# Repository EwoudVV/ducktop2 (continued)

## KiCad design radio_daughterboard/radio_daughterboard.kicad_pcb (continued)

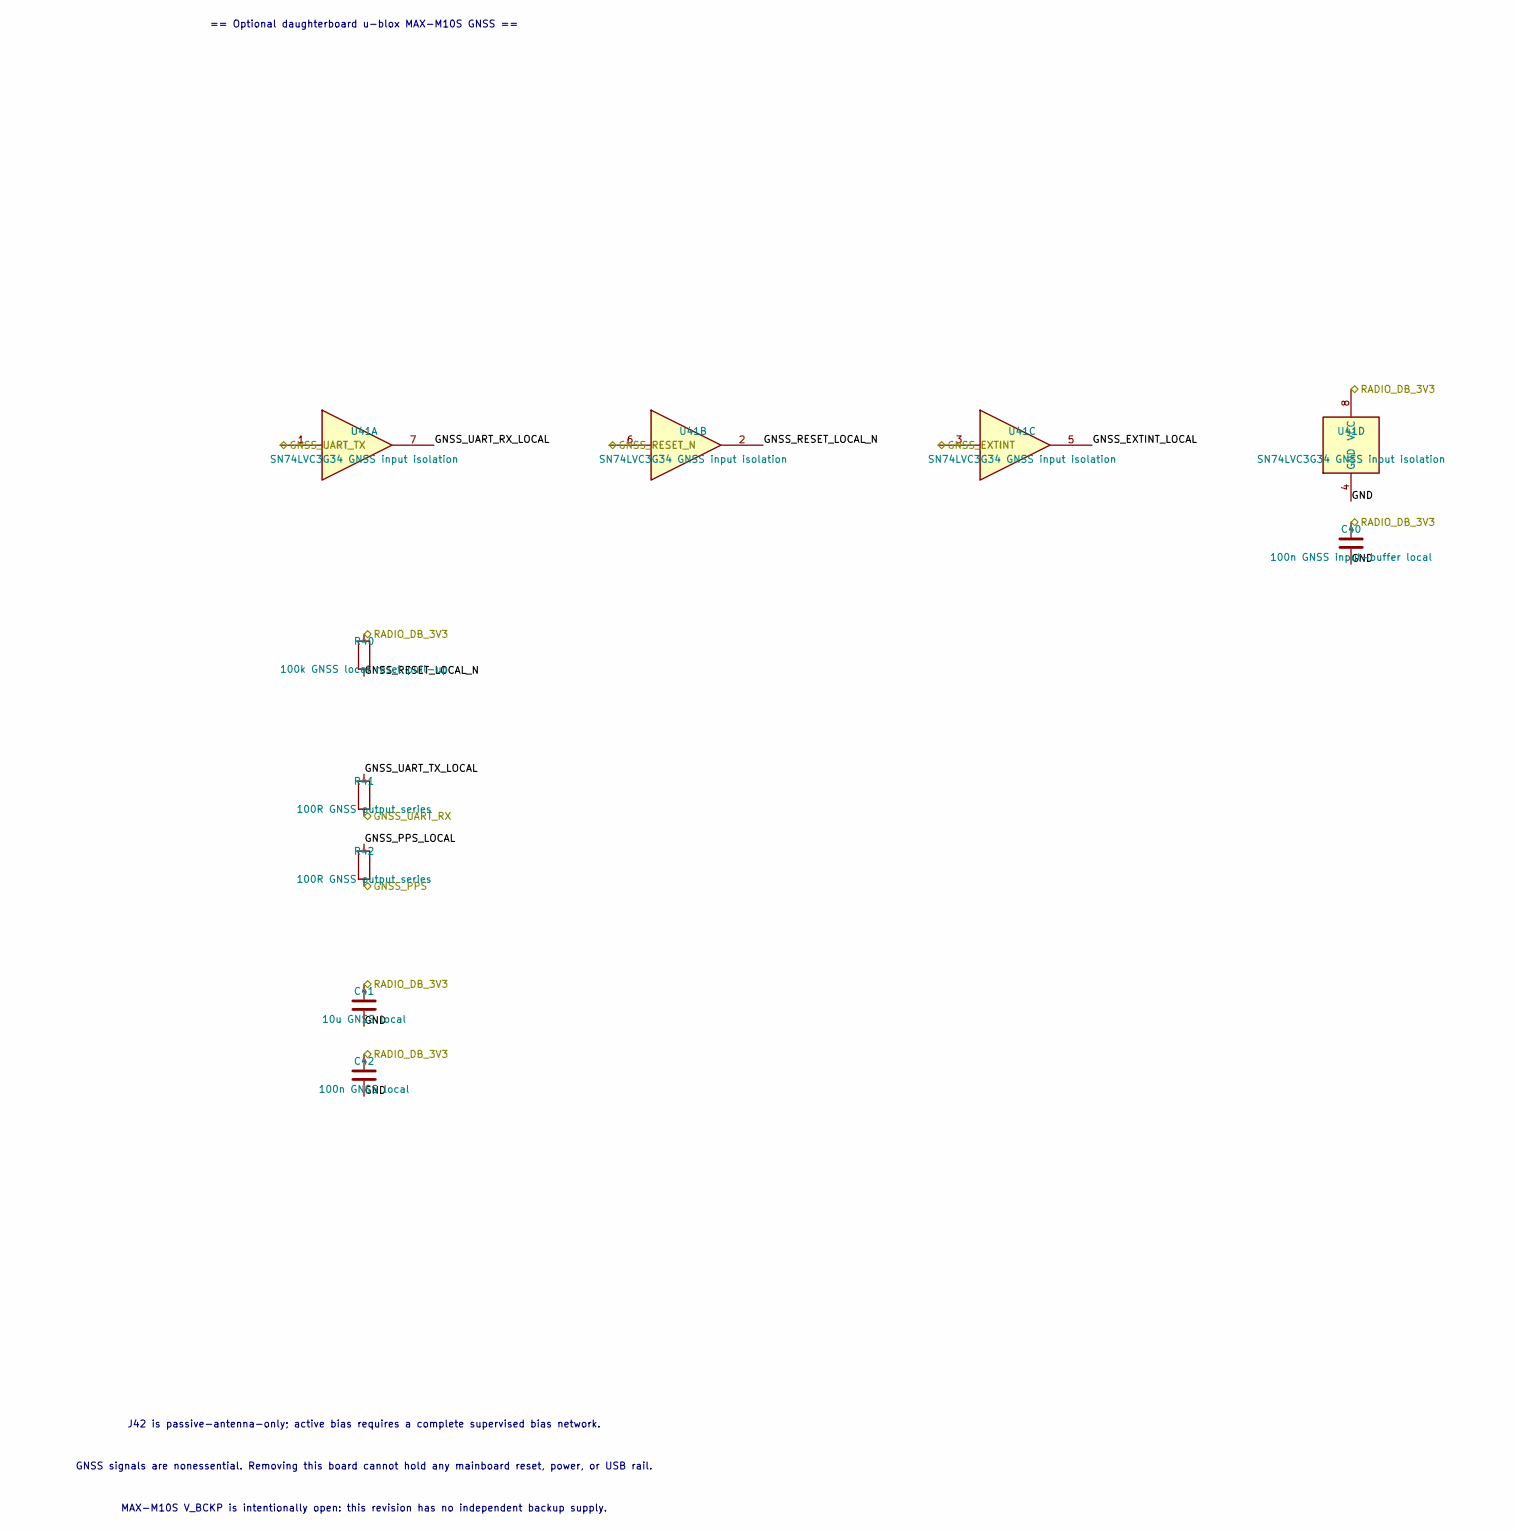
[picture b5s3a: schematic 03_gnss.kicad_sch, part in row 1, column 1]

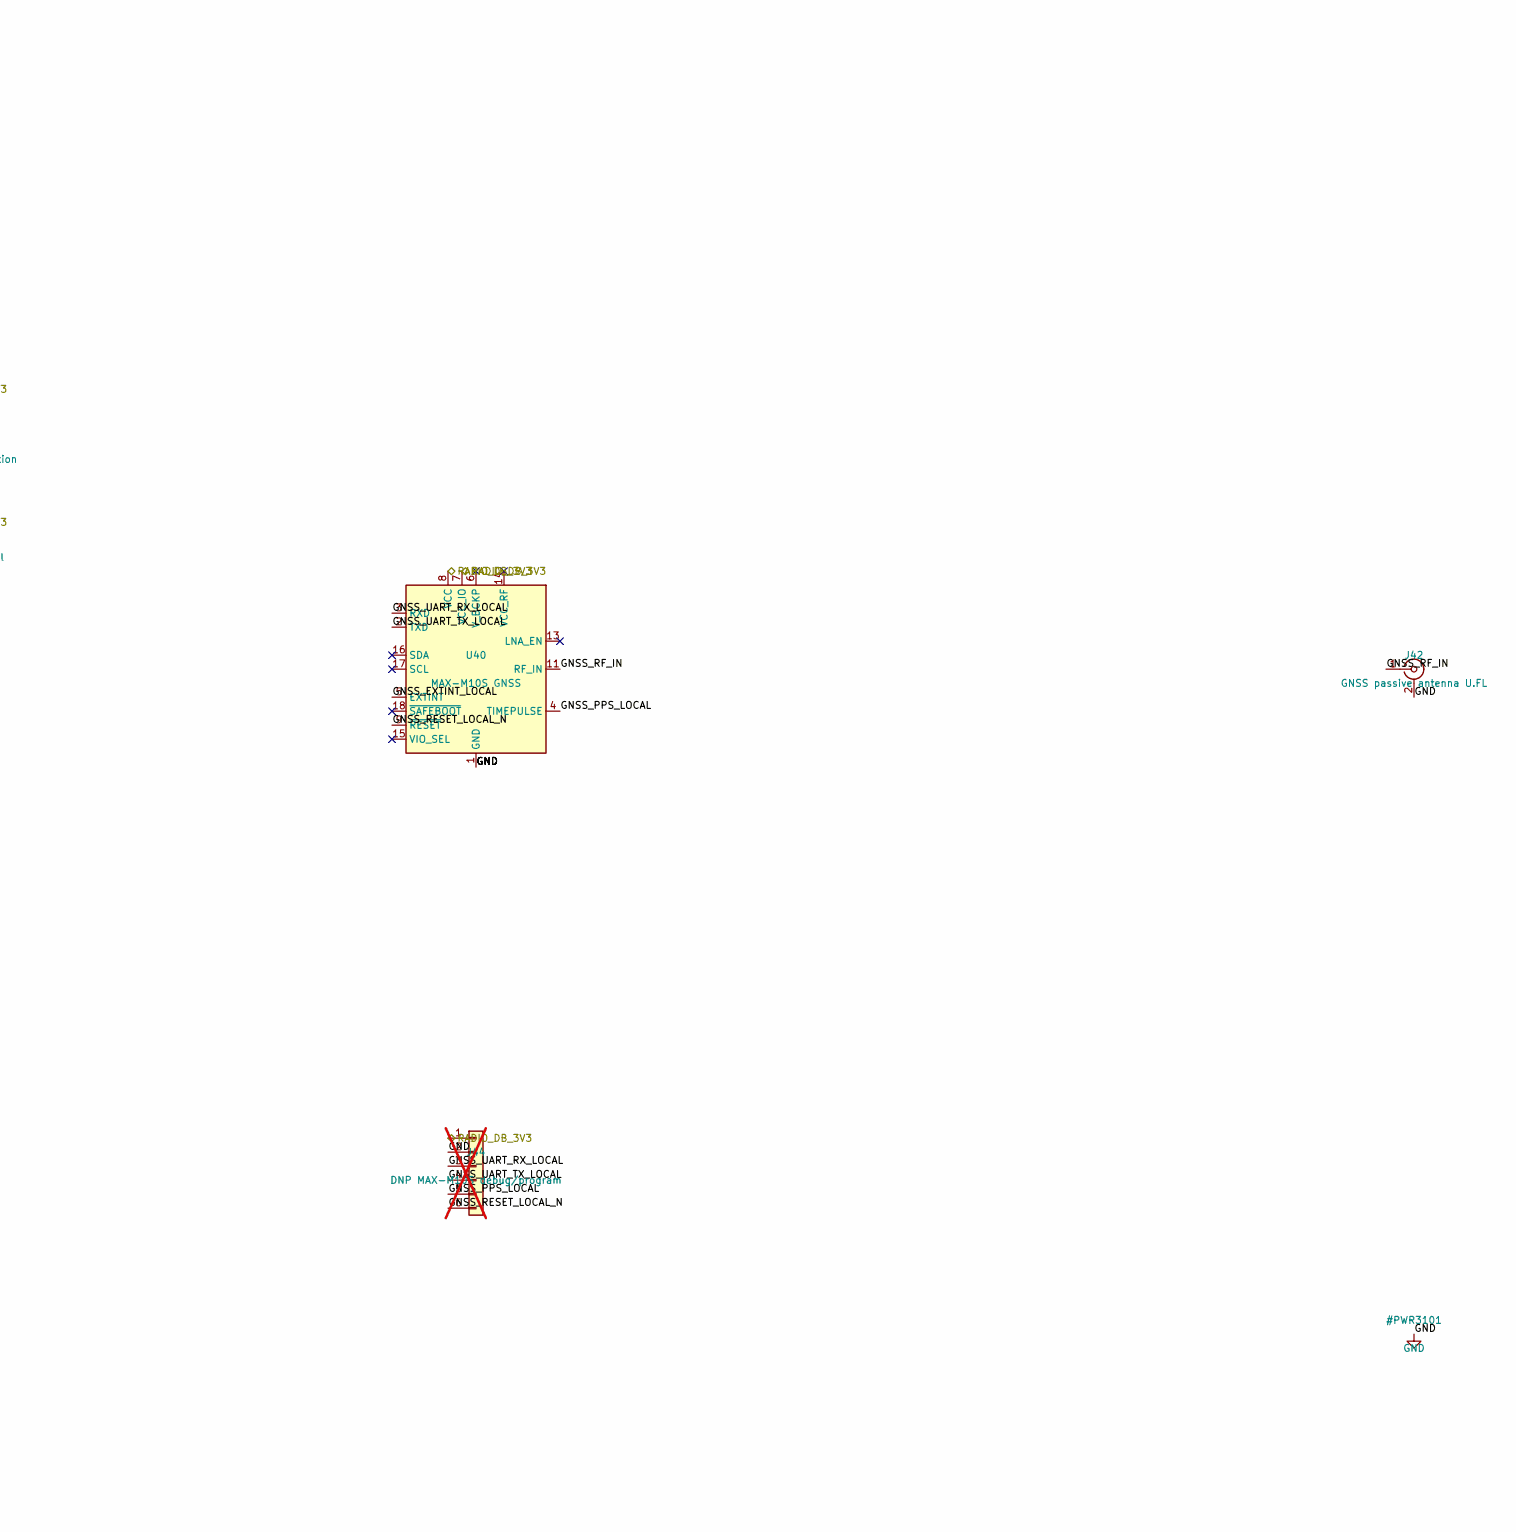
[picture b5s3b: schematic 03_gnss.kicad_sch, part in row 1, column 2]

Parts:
C40: 100n GNSS input-buffer local; C_0603_1608Metric; MPN GRM188R71H104KA93D
C41: 10u GNSS local; C_1206_3216Metric; MPN GRM31CR71E106KA12L
C42: 100n GNSS local; C_0603_1608Metric; MPN GRM188R71H104KA93D
J42: GNSS passive antenna U.FL; U.FL_Hirose_U.FL-R-SMT-1_Vertical; MPN U.FL-R-SMT-1(01)
J44: DNP MAX-M10S debug/program; PinHeader_1x06_P2.54mm_Vertical; not fitted
R40: 100k GNSS local reset pull-up; R_0603_1608Metric; MPN RC0603FR-07100KL
R41, R42: 100R GNSS output series; R_0603_1608Metric; MPN RC0603FR-07100RL
U40: MAX-M10S GNSS; ublox_MAX; MPN MAX-M10S-00B
U41: SN74LVC3G34 GNSS input isolation; VSSOP-8_2.3x2mm_P0.5mm; MPN SN74LVC3G34DCUR

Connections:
/GNSS/GNSS_EXTINT_LOCAL: U40.5 (EXTINT), U41.5
/GNSS/GNSS_PPS_LOCAL: J44.5, R42.1, U40.4 (TIMEPULSE)
/GNSS/GNSS_RESET_LOCAL_N: J44.6, R40.2, U40.9 (~RESET), U41.2
/GNSS/GNSS_RF_IN: J42.1 (In), U40.11 (RF_IN)
/GNSS/GNSS_UART_RX_LOCAL: J44.3, U40.3 (RXD), U41.7
/GNSS/GNSS_UART_TX_LOCAL: J44.4, R41.1, U40.2 (TXD)
/GNSS_EXTINT: U41.3; also elsewhere on the board
/GNSS_PPS: R42.2; also elsewhere on the board
/GNSS_RESET_N: U41.6; also elsewhere on the board
/GNSS_UART_RX: R41.2; also elsewhere on the board
/GNSS_UART_TX: U41.1; also elsewhere on the board
/RADIO_DB_3V3: C40.1, C41.1, C42.1, J44.1, R40.1, U40.7 (VCC_IO), U40.8 (VCC), U41.8 (VCC); also elsewhere on the board
GND: C40.2, C41.2, C42.2, J42.2 (Ext), J44.2, U40.1 (GND), U40.10 (GND), U40.12 (GND), U41.4 (GND); also elsewhere on the board

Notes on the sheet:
== Optional daughterboard u-blox MAX-M10S GNSS ==
J42 is passive-antenna-only; active bias requires a complete supervised bias network.
GNSS signals are nonessential. Removing this board cannot hold any mainboard reset, power, or USB rail.
MAX-M10S V_BCKP is intentionally open: this revision has no independent backup supply.

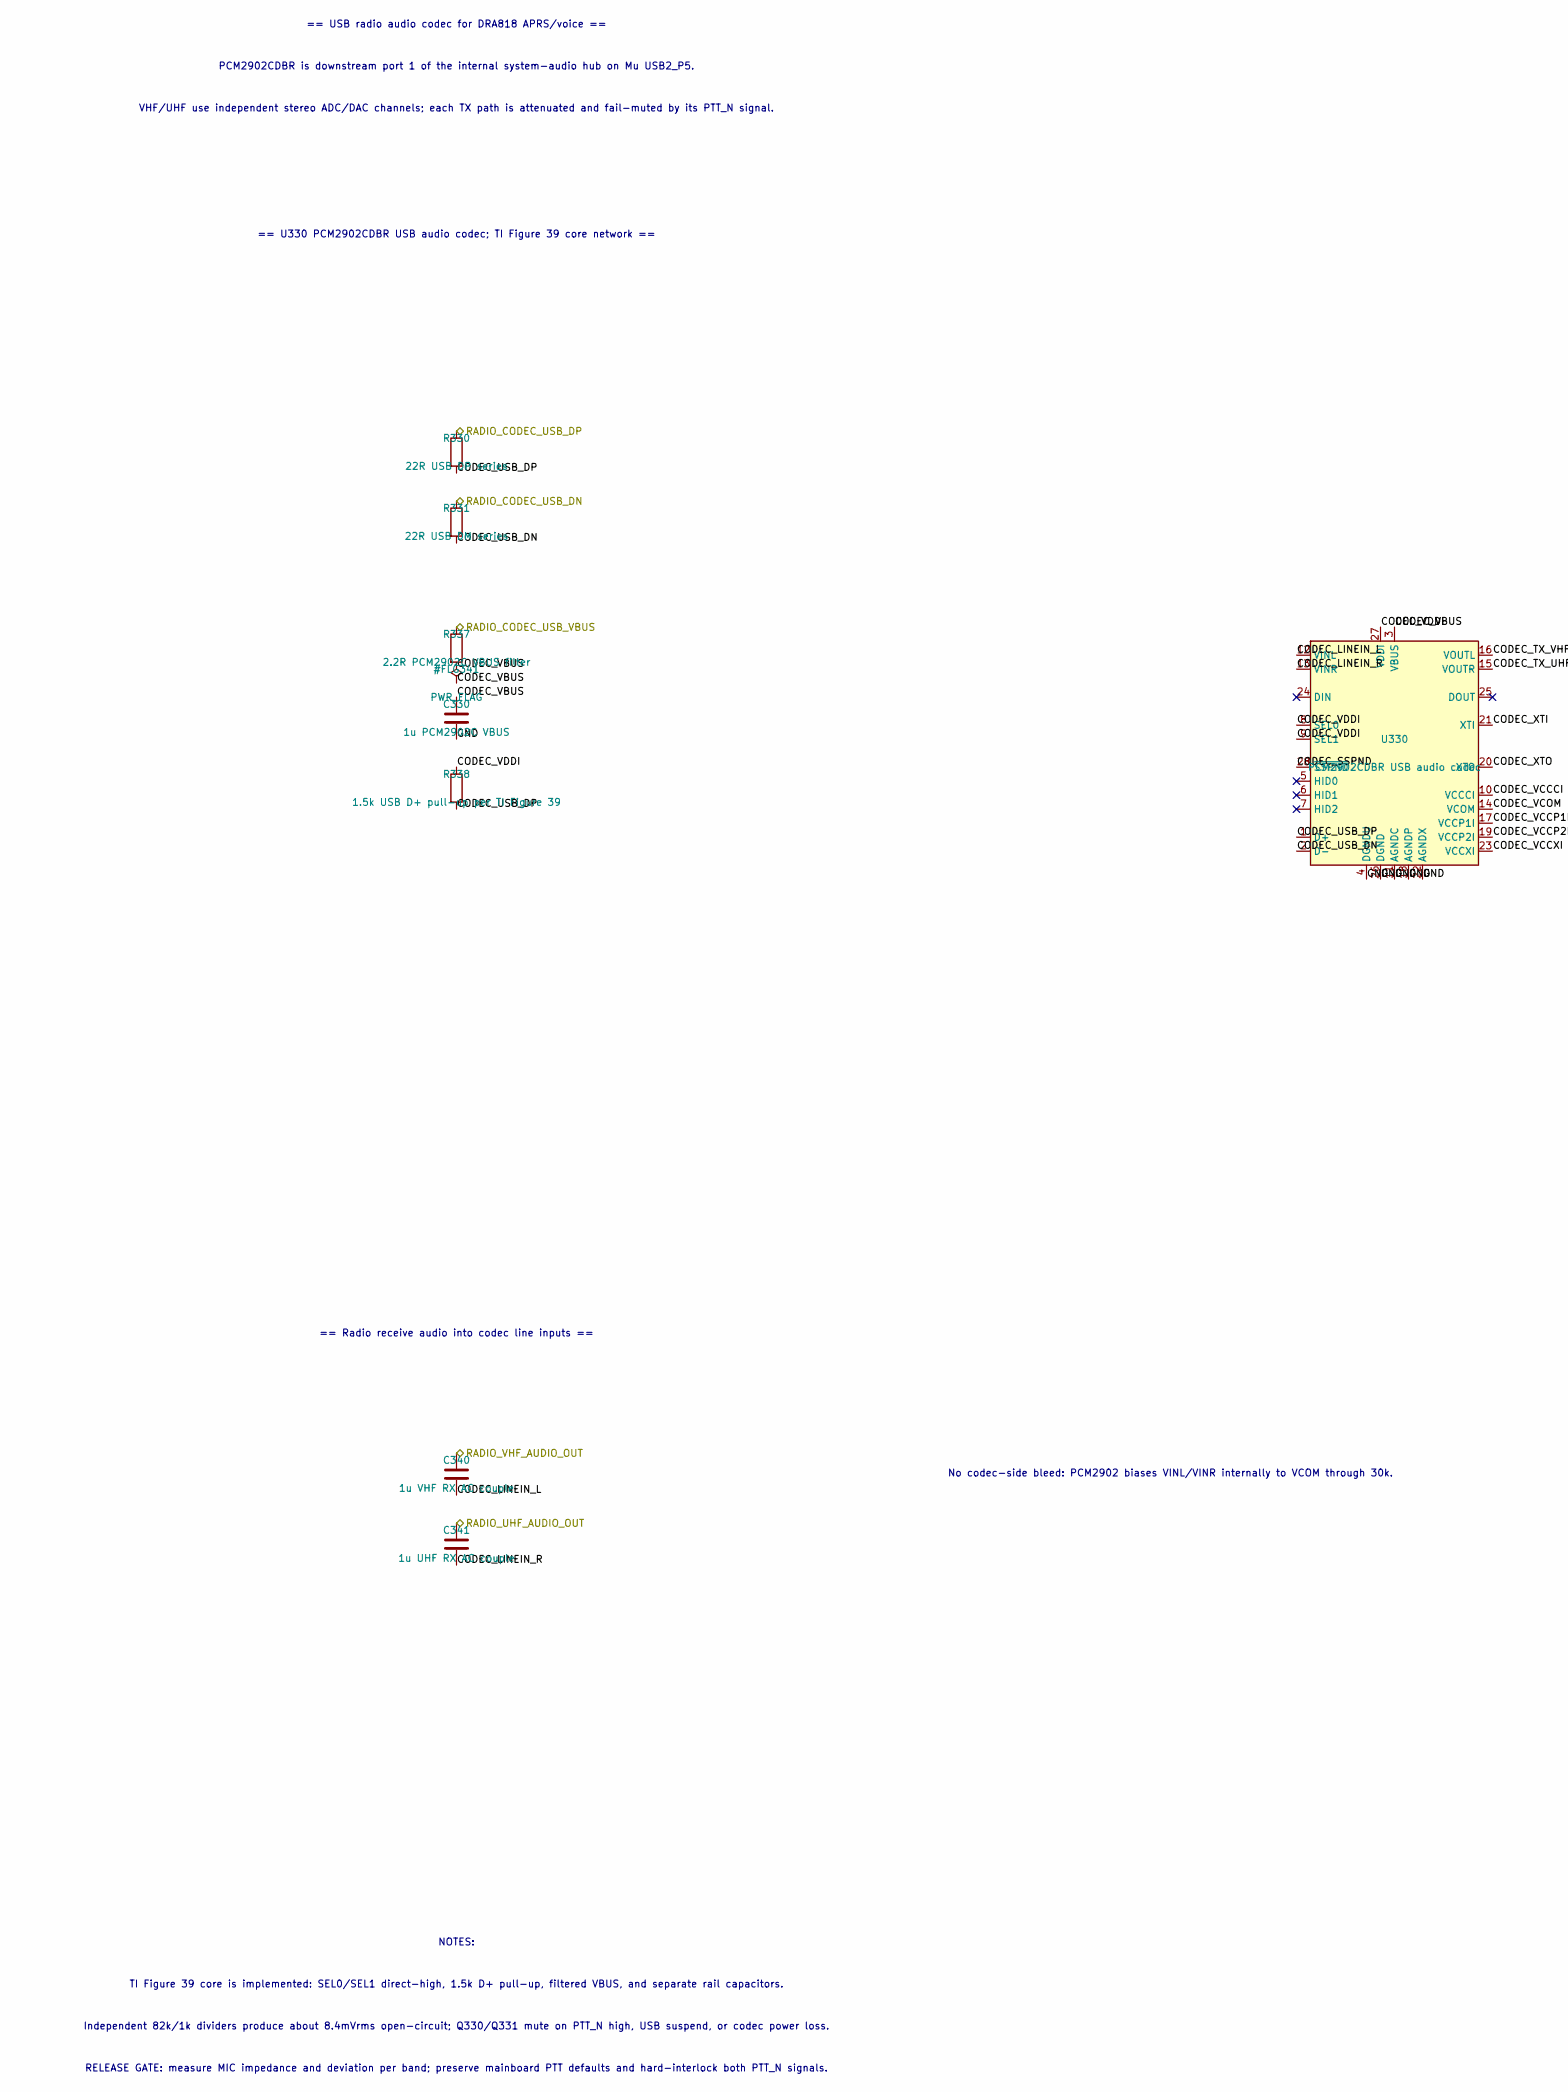
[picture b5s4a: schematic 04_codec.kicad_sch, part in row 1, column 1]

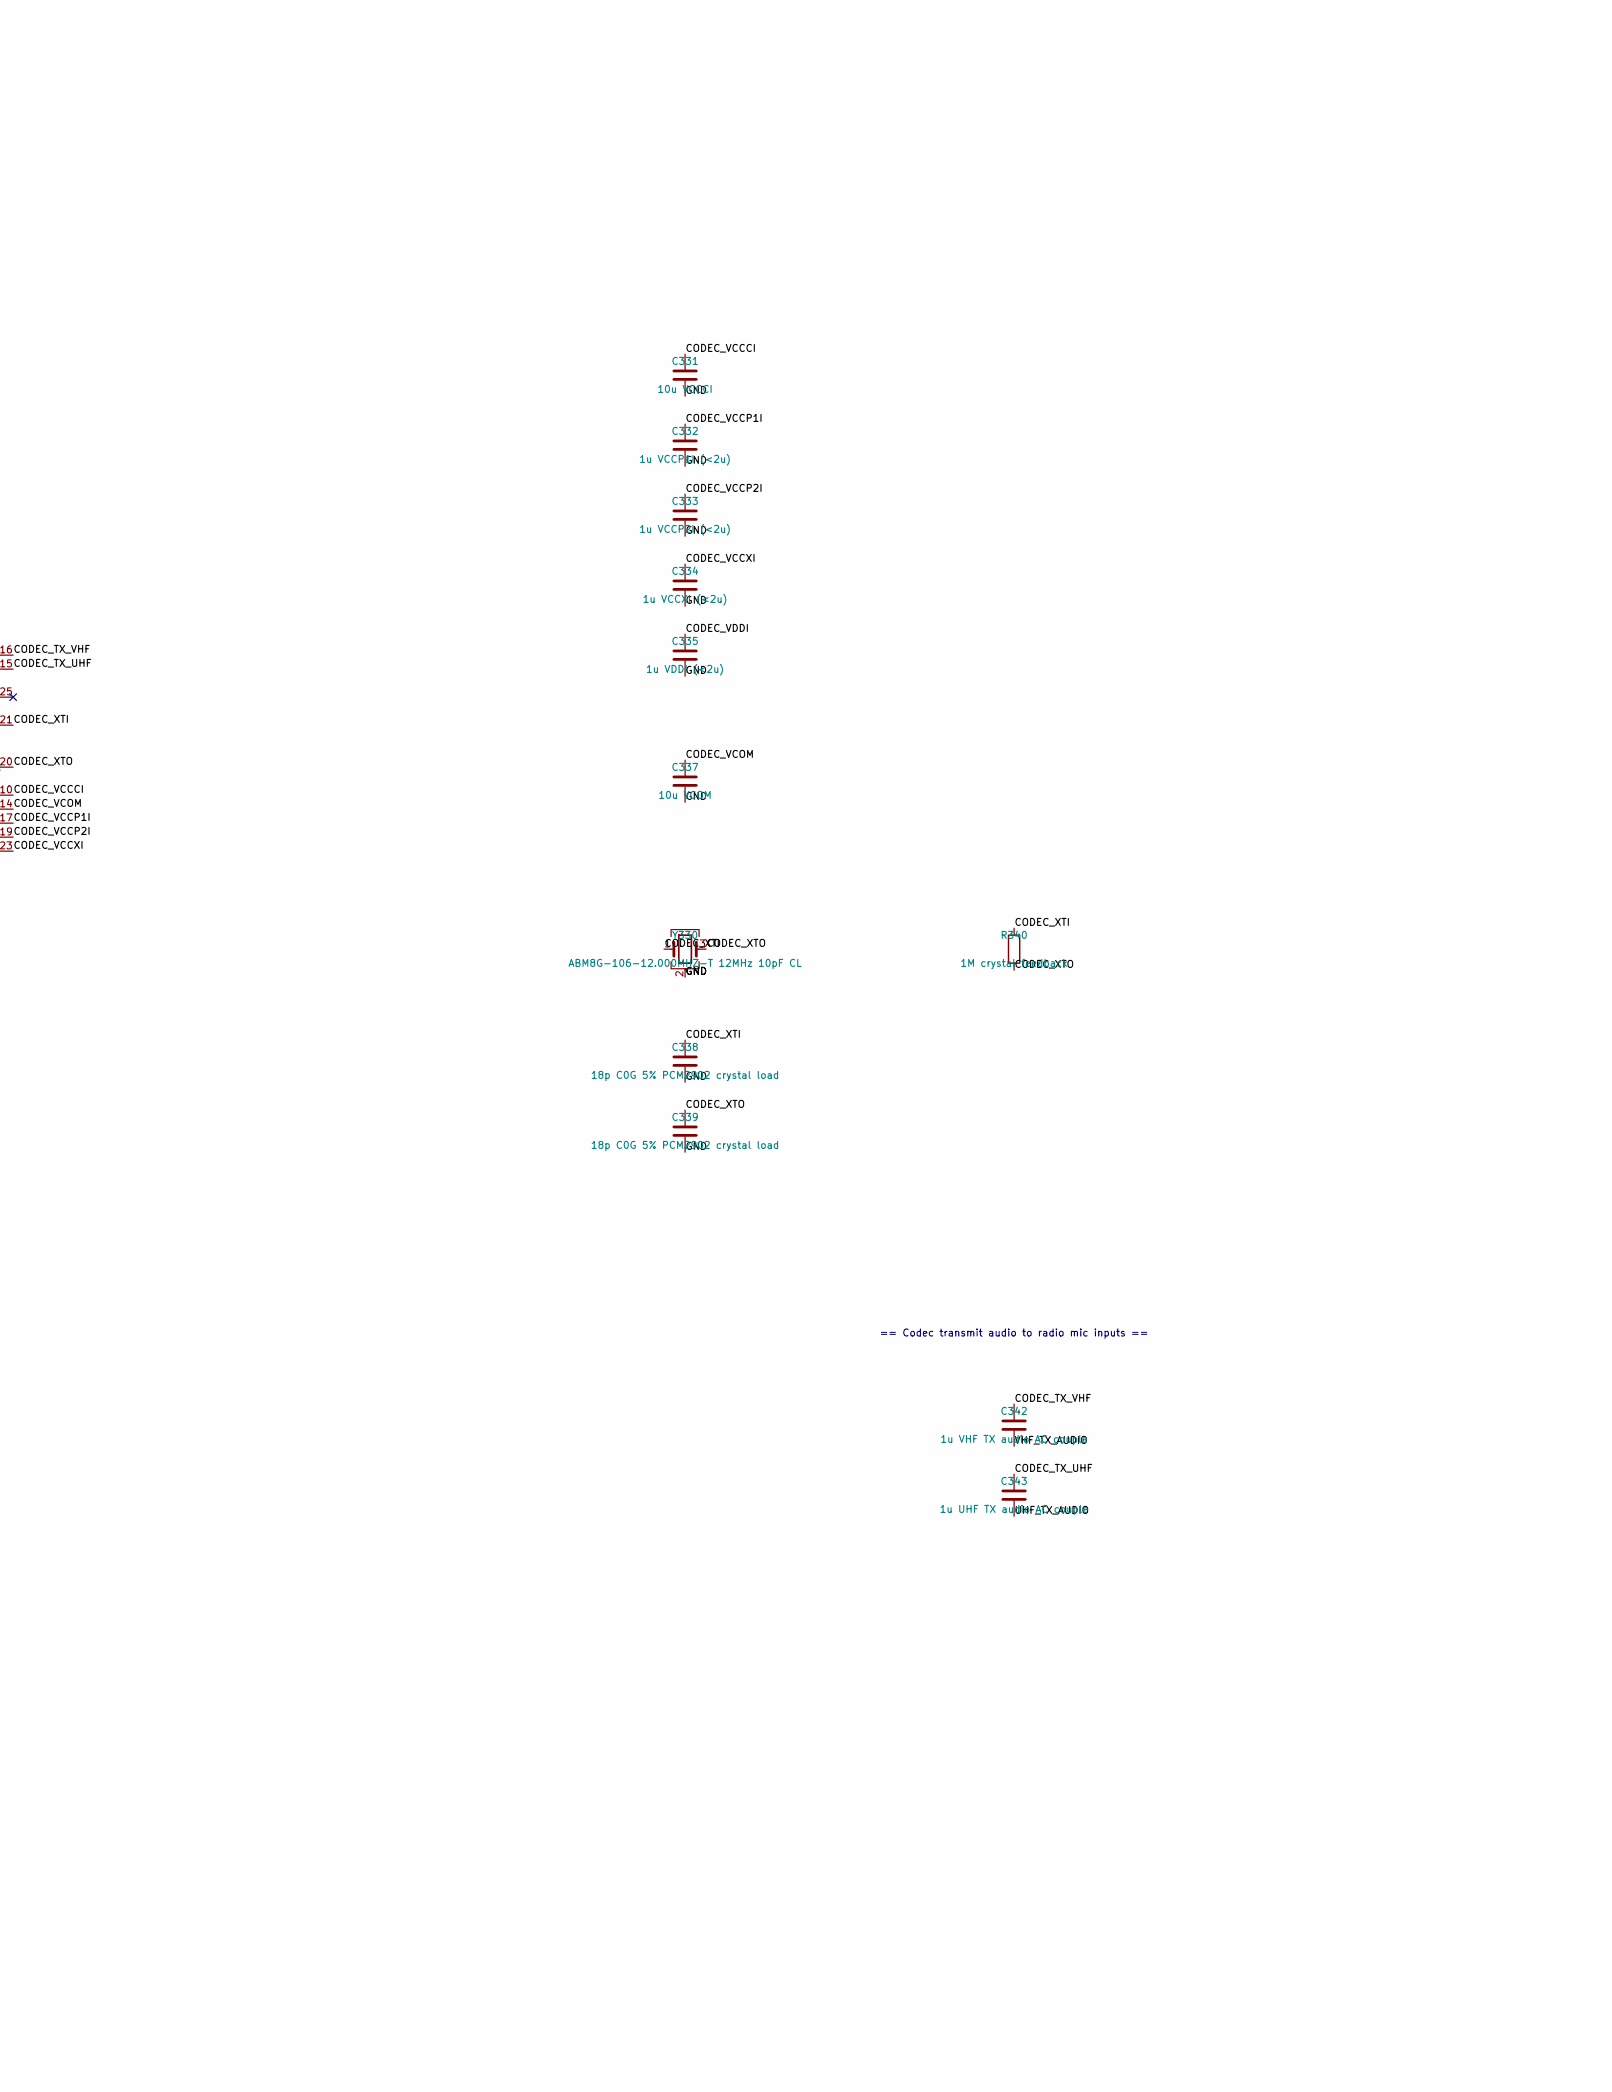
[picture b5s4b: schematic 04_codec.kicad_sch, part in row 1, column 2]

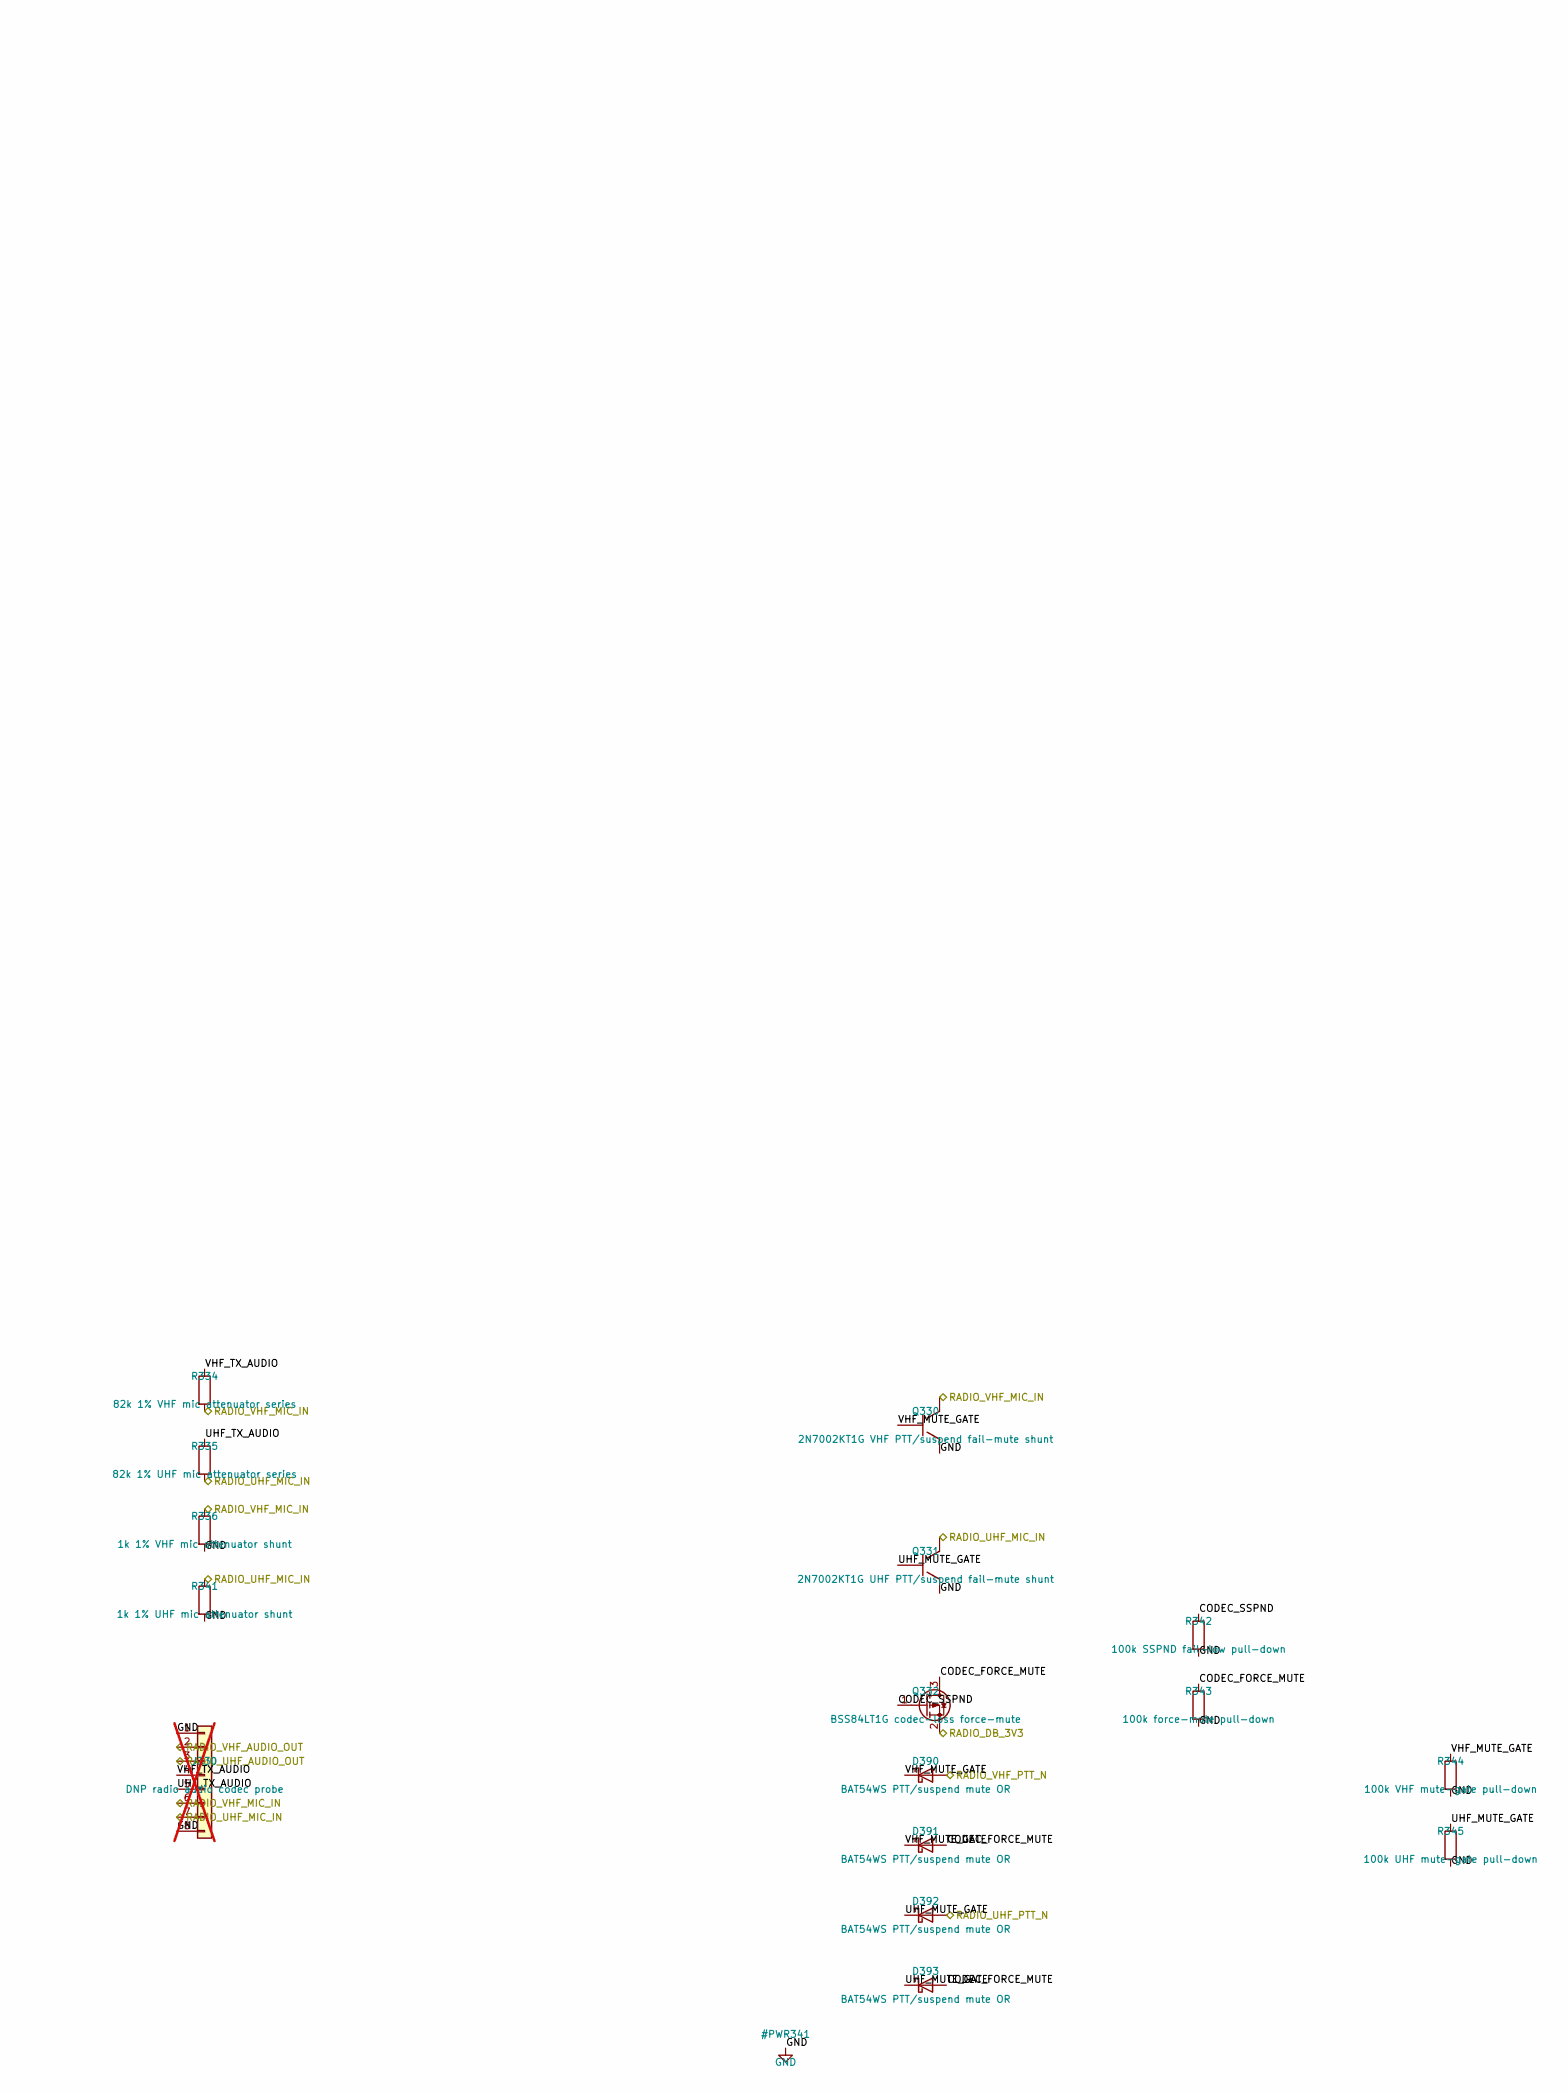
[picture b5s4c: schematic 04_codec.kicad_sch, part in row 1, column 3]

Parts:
C330: 1u PCM2902C VBUS; C_0805_2012Metric; MPN GRM21BR71A105KA01L
C331: 10u VCCCI; C_1206_3216Metric; MPN GRM31CR71E106KA12L
C332: 1u VCCP1I (<2u); C_0805_2012Metric; MPN GRM21BR71A105KA01L
C333: 1u VCCP2I (<2u); C_0805_2012Metric; MPN GRM21BR71A105KA01L
C334: 1u VCCXI (<2u); C_0805_2012Metric; MPN GRM21BR71A105KA01L
C335: 1u VDDI (<2u); C_0805_2012Metric; MPN GRM21BR71A105KA01L
C337: 10u VCOM; C_1206_3216Metric; MPN GRM31CR71E106KA12L
C338, C339: 18p C0G 5% PCM2902 crystal load; C_0603_1608Metric; MPN GRM1885C1H180JA01D
C340: 1u VHF RX AC couple; C_0805_2012Metric; MPN GRM21BR71A105KA01L
C341: 1u UHF RX AC couple; C_0805_2012Metric; MPN GRM21BR71A105KA01L
C342: 1u VHF TX audio AC couple; C_0805_2012Metric; MPN GRM21BR71A105KA01L
C343: 1u UHF TX audio AC couple; C_0805_2012Metric; MPN GRM21BR71A105KA01L
D390, D391, D392, D393: BAT54WS PTT/suspend mute OR; D_SOD-323; MPN BAT54WS-7-F
J330: DNP radio audio codec probe; PinHeader_1x08_P2.54mm_Vertical; not fitted
Q330: 2N7002KT1G VHF PTT/suspend fail-mute shunt; SOT-23; MPN 2N7002KT1G
Q331: 2N7002KT1G UHF PTT/suspend fail-mute shunt; SOT-23; MPN 2N7002KT1G
Q332: BSS84LT1G codec-loss force-mute; SOT-23; MPN BSS84LT1G
R330: 22R USB DP series; R_0603_1608Metric; MPN RC0603FR-0722RL
R331: 22R USB DM series; R_0603_1608Metric; MPN RC0603FR-0722RL
R334: 82k 1% VHF mic attenuator series; R_0603_1608Metric; MPN RC0603FR-0782KL
R335: 82k 1% UHF mic attenuator series; R_0603_1608Metric; MPN RC0603FR-0782KL
R336: 1k 1% VHF mic attenuator shunt; R_0603_1608Metric; MPN RC0603FR-071KL
R337: 2.2R PCM2902C VBUS filter; R_0603_1608Metric; MPN RC0603FR-072R2L
R338: 1.5k USB D+ pull-up per TI Figure 39; R_0603_1608Metric; MPN RC0603FR-071K5L
R340: 1M crystal feedback; R_0603_1608Metric; MPN RC0603FR-071ML
R341: 1k 1% UHF mic attenuator shunt; R_0603_1608Metric; MPN RC0603FR-071KL
R342: 100k SSPND fail-low pull-down; R_0603_1608Metric; MPN RC0603FR-07100KL
R343: 100k force-mute pull-down; R_0603_1608Metric; MPN RC0603FR-07100KL
R344: 100k VHF mute-gate pull-down; R_0603_1608Metric; MPN RC0603FR-07100KL
R345: 100k UHF mute-gate pull-down; R_0603_1608Metric; MPN RC0603FR-07100KL
U330: PCM2902CDBR USB audio codec; SSOP-28_5.3x10.2mm_P0.65mm; MPN PCM2902CDBR
Y330: ABM8G-106-12.000MHZ-T 12MHz 10pF CL; Crystal_SMD_3225-4Pin_3.2x2.5mm; MPN ABM8G-106-12.000MHZ-T

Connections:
/RADIO_CODEC_USB_DN: R331.1; also elsewhere on the board
/RADIO_CODEC_USB_DP: R330.1; also elsewhere on the board
/RADIO_CODEC_USB_VBUS: R337.1; also elsewhere on the board
/RADIO_DB_3V3: Q332.2 (S); also elsewhere on the board
/RADIO_UHF_AUDIO_OUT: C341.1, J330.3; also elsewhere on the board
/RADIO_UHF_MIC_IN: J330.7, Q331.3 (D), R335.2, R341.1; also elsewhere on the board
/RADIO_UHF_PTT_N: D392.2 (A); also elsewhere on the board
/RADIO_VHF_AUDIO_OUT: C340.1, J330.2; also elsewhere on the board
/RADIO_VHF_MIC_IN: J330.6, Q330.3 (D), R334.2, R336.1; also elsewhere on the board
/RADIO_VHF_PTT_N: D390.2 (A); also elsewhere on the board
/USB Radio Audio/CODEC_FORCE_MUTE: D391.2 (A), D393.2 (A), Q332.3 (D), R343.1
/USB Radio Audio/CODEC_LINEIN_L: C340.2, U330.12 (VINL)
/USB Radio Audio/CODEC_LINEIN_R: C341.2, U330.13 (VINR)
/USB Radio Audio/CODEC_SSPND: Q332.1 (G), R342.1, U330.28 (~SSPND)
/USB Radio Audio/CODEC_TX_UHF: C343.1, U330.15 (VOUTR)
/USB Radio Audio/CODEC_TX_VHF: C342.1, U330.16 (VOUTL)
/USB Radio Audio/CODEC_USB_DN: R331.2, U330.2 (D-)
/USB Radio Audio/CODEC_USB_DP: R330.2, R338.2, U330.1 (D+)
/USB Radio Audio/CODEC_VBUS: C330.1, R337.2, U330.3 (VBUS)
/USB Radio Audio/CODEC_VCCCI: C331.1, U330.10 (VCCCI)
/USB Radio Audio/CODEC_VCCP1I: C332.1, U330.17 (VCCP1I)
/USB Radio Audio/CODEC_VCCP2I: C333.1, U330.19 (VCCP2I)
/USB Radio Audio/CODEC_VCCXI: C334.1, U330.23 (VCCXI)
/USB Radio Audio/CODEC_VCOM: C337.1, U330.14 (VCOM)
/USB Radio Audio/CODEC_VDDI: C335.1, R338.1, U330.8 (SEL0), U330.9 (SEL1), U330.27 (VDDI)
/USB Radio Audio/CODEC_XTI: C338.1, R340.1, U330.21 (XTI), Y330.1
/USB Radio Audio/CODEC_XTO: C339.1, R340.2, U330.20 (XTO), Y330.3
/USB Radio Audio/UHF_MUTE_GATE: D392.1 (K), D393.1 (K), Q331.1 (G), R345.1
/USB Radio Audio/UHF_TX_AUDIO: C343.2, J330.5, R335.1
/USB Radio Audio/VHF_MUTE_GATE: D390.1 (K), D391.1 (K), Q330.1 (G), R344.1
/USB Radio Audio/VHF_TX_AUDIO: C342.2, J330.4, R334.1
GND: C330.2, C331.2, C332.2, C333.2, C334.2, C335.2, C337.2, C338.2, C339.2, J330.1, J330.8, Q330.2 (S), Q331.2 (S), R336.2, R341.2, R342.2, R343.2, R344.2, R345.2, U330.4 (DGNDU), U330.11 (AGNDC), U330.18 (AGNDP), U330.22 (AGNDX), U330.26 (DGND), Y330.2 (G), Y330.4 (G); also elsewhere on the board

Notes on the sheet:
== USB radio audio codec for DRA818 APRS/voice ==
PCM2902CDBR is downstream port 1 of the internal system-audio hub on Mu USB2_P5.
VHF/UHF use independent stereo ADC/DAC channels; each TX path is attenuated and fail-muted by its PTT_N signal.
== U330 PCM2902CDBR USB audio codec; TI Figure 39 core network ==
== Radio receive audio into codec line inputs ==
No codec-side bleed: PCM2902 biases VINL/VINR internally to VCOM through 30k.
== Codec transmit audio to radio mic inputs ==
NOTES:
TI Figure 39 core is implemented: SEL0/SEL1 direct-high, 1.5k D+ pull-up, filtered VBUS, and separate rail capacitors.
Independent 82k/1k dividers produce about 8.4mVrms open-circuit; Q330/Q331 mute on PTT_N high, USB suspend, or codec power loss.
RELEASE GATE: measure MIC impedance and deviation per band; preserve mainboard PTT defaults and hard-interlock both PTT_N signals.

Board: 4 copper layers, 126 parts (1 on the bottom side), 95 nets, no tracks yet.
